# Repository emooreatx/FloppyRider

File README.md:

# FloppyRider

Full-featured DIY PC-compatible 8-inch Diskette drive based on the IBM 51TD.

## Project events

__New enclosure and AC power supply (v1.0) (2023/05/02)__

__Third revision of the controller (v2.1) (2022/12/03): Added an improved write protection mechanism and support for installing an external write protection switch.__ __Fabrication files released: [V2 fabrication files](./pcb)__

__Second revision (2022/06/24):__ I have added a transistor to drive the write/erase-gate signals on the IBM drive. I have noticed that write/erase-gate have a very low input impedance (90 ohms each, could that be a safety measure to make harder to accidentally drive the signal high?) that is way over-spec for the 74LS logic to drive properly. The prototype worked by pure luck but trying with other 74LS components the signal level was too low to enable the gates so the device was only capable of reading. The solution is to include a transistor to drive that signals up to acceptable levels.

__Initial release (2022/06/09)__

## Introduction

This project shows how to create an adapter to be able to use IBM 8-inch Diskette drives with a standard PC floppy controller. It includes a controller/adapter, power supply and 3D-printed enclosure designed to connect an IBM 51TD disk drive to a regular PC floppy controller.

In theory it may work also with IBM 31SD drives but I don't have one so it is untested for them.

The current production version is capable of reading, writing and formatting Diskette 1,Diskette 2 (SD) and Diskette 2D (DD) types on a 51TD disk drive.

The IBM 51TD was used in the IBM Displaywriter, System/36, System/38, and other machines.

If you like it or want to make your unit drop me a message to inmbolmie [AT] gmail.com

## Videos

Video showing general operation connected to an IBM 5160: [FloppyRider 8-inch drive for PCs](https://www.youtube.com/watch?v=_m2nTry7Z7E)

Video showing the adapter in action, here it is used to make an 8-inch diskette MSDOS-bootable: [Booting MSDOS from an IBM 51TD 8-inch drive](https://www.youtube.com/watch?v=TbLUqG_d6FU)

Using the adapter to image a 33FD-formatted diskette with Imagedisk: [Imaging on a PC an IBM 8-inch diskette with a 51TD diskette drive, Imagedisk and FloppyRider](https://www.youtube.com/watch?v=4pZ3qMAHVGs)

This project was inspired by CuriousMarc's video about data recovery from 8-inch floppies. This kind of converter is something Master Ken would have made like in five minutes using a Teensy, in case they wanted to use a genuine IBM Diskette drive in their data recovery adventure.

[Fossil Data Part 2: 8-Inch IBM Floppy Data Recovery](https://www.youtube.com/watch?v=5FVwheTVWko)

## Hardware

There are three main components on this project, the drive controller, the power supply and the 3D-printed enclosure

### Drive controller

The adapter hardware is pretty straightforward and can be made cheapily with very low-cost components:

* Pin headers and IDC ribbon cables
* JST-XH 5A Connector for DC input
* Arduino ProMicro microcontroller board (5V)
* 74LS02
* 74LS06
* 74LS08
* 74LS74
* 12x1K resistors
* 1x4,7K resistor
* NPN transistor

### Power supply

The 31SD and 51TD disk drives have pretty hefty power requirements, as you will need to provide them with:

* AC mains power for the disk rotating motor (on a separate connector)
* +24V at 12W (on the 36-pin idc connector)
* +5V (on the 36-pin idc connector)
* -5V (on the 36-pin idc connector)

I have designed a custom power supply based on discrete AC-DC and DC-DC converters. It is not so cheap to make as the controller as the discrete converters are expensive. The required components are:

* MeanWell IMR-20-24 AC to +24V DC conversion module
* Traco Power TEN 6-2421N DC to +-5V DC conversion module
* JST-XH 5A Connector for DC output
* 3x100uF 50V aluminium electrolytic capacitors
* Schurter DD21.0124.1111 AC plug module
* Schurter 4301.1024.26 fuse holder
* TE Connectivity / AMP 350834-4 connector
* 1A AC fuses

The power supply is fused, cuts both phases on AC input when switched off and connects protective earth to protective earth on the drive connector. The individual modules provide also short-circuit and overload protection.

__Warning, the power supply is compatible with both 110V and 220V drives through the IMR-20-24 module, but does not make any conversion on the AC input that is passed directly to the drive motor. So even with this supply you cannot use a 110V drive on 220V AC line or a 220V drive on 110V AC line. So make sure that your drive is compatible with your AC line voltage__

### 3D-printed enclosure

Having a naked 51TD isn't ideal for extended use so I have designed a 3D-printed case that can be made using regular printers and is inspired on the IBM drive enclosures of the era.

Note that this is a BIG print job, has many parts and can take like a full week of non-stop printing to make. It is also tricky to assemble, as some parts have to be glued-in to keep the part design and printing as simple as possible. The total printing material required is around 850-1000 grams depending on the infill used on some parts.

You also need at least a 270 x 210mm sized 3d-printer bed to be able to print this. The biggest pieces measured by printed area are the side panels.

I include STL files for all the parts as well as the Freecad 3D model.

You can get the STL and design files in the __case__ directory.

## Software

You can get the Arduino source code for the ProMicro in the __FloppyRider__ directory. You can program it using the regular Arduino IDE.

## KiCad Project

You can get the current project files in the __KiCad__ directory. The PCB design files and gerbers are now available if you want to make your own boards :  [V2 fabrication files](./pcb)

Note that the files have been created with Kicad v6.

## Warning about some floppy controllers

It seems that some floppy controllers may ground the signals to the floppy drive when the computer is switched off. If you have a diskettte inserted and engaged when this happens, that can lead to the track where the head is currently positioned to be erased.

If you are working with important media be careful about this, and __turn on the disk drive only after the computer is switched on, and remove the diskette or the power to the disk drive before the computer is switched off.__

__The version 2 board improves this situation__ because when the write protection switch is engaged, the Write/Erase Gate signals for the 8" drive are physically disconnected from the incoming write signals, so you won't accidentally erase any data __if write protection is engaged__, even if the host floppy controller grounds all the interface signals. This makes the adapter safer for using in disk imaging tasks.

## Operation

These are the main points that need to be carried out for conversion:

#### Logic levels

The PC floppy signals are open collector low-level active, while the IBM signals are push-pull high-active. The 74 series chips provide most of the conversion.

All the signals are gated by the "drive select" PC signal for the adapter to be able to operate with another floppy drive on the same cable.

#### Track addressing

The PC floppy adresses tracks by a "direction" and "step" signal, and gets a "track 0" signal when the head is placed at such track. The IBM interface lacks a "track 0" signal and you control direcly the stepper motor signals "access 0" and "access 1". The ProMicro initializes the head position at track 0 at startup. From there it gets track of where the head is actually positioned and translates the required signals on both sides.

#### Write data signal.

The PC floppy write data signal generates a full pulse (falling and rising edge) for each magnetic flux transition that needs to be recorded on the disk surface, while in the IBM interface the "write data" signal records a magnetic flux transition for each signal level change (rising or falling edge). The conversion is made via the 74LS74 flip-flop.

## Connection

__As the connectors carry a powerful +24V signal, connector orientation is critical and getting it wrong, reversing or misplacing it could damage your hardware.__

### Option A: Power the drive from a compatible host system

The easier way to get all the required power rails is getting them from the original host hardware where the disk drive is enclosed. For that reason a 36-pin host connector header is provided. Note that the connector sides are mirrored to be able to use it with a cable-to-cable connection. The adapter will be placed as a bridge between the host cable and the disk drive header.

The other 36-pin header will be used with a regular IDC ribbon cable connector to connect it to the disk drive. Note that you won't be _easily_ able to use the most common 40-pin cables as the available space for the connector in the disk drive is very limited.

Not that "Pin B1" position is indicated on the silkscreen of the PCB.

### Option B: Power the drive from the independent power supply

If you have the FloppyDriver independent power supply capable of providing the required DC levels you can leave the 36-pin host pin header unconnected and provide power via a separate 5-pin JST-XH connector.

### Connection to the PC drive controller

On the other end of the adapter you have a 34-pin header for the PC standard floppy cable. The adapter is hard-wired for drive B as most PC floppy drives are.

Not that "Pin 1" position is indicated on the silkscreen of the PCB.

## External write protection

A 6-pin 2x3 pin header is provided to be able to connect an external SPDT write protection switch. In case of __using the external write protection switch, the on-board switch has to be placed in the ON position and jumper JP1 has to be removed__. Then you can control the ON-OFF write protection status from the external switch.

On the contrary, __if you are using the on-board write protection switch, the JP1 jumper has to be installed__. The jumper is not safety-critical though, as the effect of not installing it will be that the host controller will consider the write protection always disabled, but the drive will be write-protected anyway if the write protection switch is in the ON position.

## Schematics

As currently working on the production units. Subject to further modification

## PCB

Sample image of the PCBs from Kicad.

## 3D-printed case fabrication and assembly

This enclosure has been designed to be reasonably easy to print on a 3D printer with a 270 x 210mm sized bed, on regular PLA filament and in a maximum of 14 hours of printing for a single piece.

With 2mm thick walls the case is sturdy enough to be convenient to carry around the assembled unit, but obviously doesn't have the rigidity of a full-metal or ABS injection-molded enclosure.

It is designed to be assembled using 10mm M4 DIN-965 bolts and nuts. A couple of M3 bolts and nuts are also required for the power supply, and four 5mm M2,5 bolts for the controller PCB attachment. The nuts have to be soldered to the enclosure with the superglue-soda method on some places and some pieces have to be glued together. That minimal assembly allows to simplify the piece design and all the pieces can be printed without supports. In reality it would be better to print 3mm thick walls to get a better mount for the M4 bolts (they will protrude a little on 2mm walls) but that would increase notably the printing times.

Of course you can also reduce the times increasing the layer height. I printed eveything at 0,2mm layer height but 0,3 or 0,4mm could be more convenient.

All the pieces have been printed on regular PLA, no supports, 0,2mm layer heigh, infill 100% except for the base that was printed with 20% infill. The printing time for the big pieces on my printer is between 7 and 14 hours (14 for back panel). In total it took me around a week to print everything, one big piece each day. In total I used approx. 850 grams of 1,75mm filament.

Now I will give some assembly tips.

There are two versions of the front panel, one with a window for a 25x25mm badge and one without it.

To assemble the unit first you have to join the front panel to the base with two bolts and two nuts. You will have to drill the holes on the front panel baseas they are not included. These like other holes are not included because I think that drilling them yourself will give a better piece alignment. Drill them with a 4mm drill.

For the back panel the attachment is similar but you will have to be able to remove it without access to the nuts so the nuts will have to be fixed with the superglue+soda method or any other similar system. That way you will be able to tighten the bolts from under the base when the drive is in place

Now place the drive inside and align it to the holes on the right side (looking from the front) panel and the right side of the front panel. Be gentle with the front lever of the unit as it is quite fragile, it has to be engaged to go inside the slit.

The left panel will be far from the drive, so you will have to print three drive fitting blocks and solder them to the base using superglue like shown here (there is another place not shown on the picture to place a fitting to the right). The inner fitting is for the drive and the outer fitting is for the panel. You can in theory use very long M4 bolt to stick the panel to the drive, but it is better to use two 10mm short bolts instead. The holes on the fittings have to be aligned to the holes on the drive and panel.

You have to assemble also four panel fittings on top of the front and back pieces to secure the side panels. They are shown on the first picture near the top. They have a nut each on back. Be sure to align them to the holes on the side panels. On the final design the fittings are a little lower than on the picture because I discovered that they interferred with the power supply pcb position and because of that they were tricky to fix to the back panel.

To align the fittings it would be more convenient to separate the front and back panels from the base. Now prepare the top, left and right panels that have to be glued together. Then put everything upside down together and attach and glue the fittings to the front and back panels.

Now prepare the cable, you need approx. a 60cm 36-pin IDC ribbon cable. Note that the drive pin header is a tight fit for the cable, so you cannot use anything else bigger, like the more common 40-pin ribbon cable connectors.

The cable goes under the drive. There is a channel made on the base to allow the cable to go under the drive mounting feet.

Check carefully for Pin-1 position. On the picture the red cable indicates pin-1 and goes to the left of the connector as seen looking the drive from the right side.

Now prepare the back panel, mounting the power supply with M3 bolts and nuts. The controller is mounted on top of the PCB-holder piece using M2,5 bolts. Connect the supply and the controller using a suitable 5-pin JST-XH cable. Connect the drive 36-pin ribbon cable before the controller is assembled. Check carefully for pin-1 position, on the PCB is marked as "Pin B1". Note that the red cable goes to that side.

Do not forget to put in place the write protection switch between the controller and the back panel. You will need to drill a 2mm hole in the center of the switch to slide it onto the switch lever mounted on the PCB. To insert it you have to bend the back "ears" and straighten them again after inserted. The on-board swith is very simple, you may want to change it for a proper external SPDT switch as the controller PCB supports it.  

Switch to the right is write protected, switch to the left is write enabled. I didn't include any lettering to keep the printing simple, but you can add it or put on a sticker to indicate it.

Now you can put in place the back panel and tighten the bolts from under the base to hold it in position.

When the panel is in, place attach the 51TD power connector to the power supply. This connector can only go one way.

Now finally mount the center section. The top, left and right panels were already glued together. Attach them using M4 bolts to the drive on the left, to the fitting glued to the base on the right, and to the front and back panels on the top using four bolts. Do not overtighten anything as you risk to rip the nuts from the pieces and in general is not needed.

This a sample of how could the unit look on the back connected to a PC. If you are going to have a setup like this add some anti-slip rubber feet under the drive base.

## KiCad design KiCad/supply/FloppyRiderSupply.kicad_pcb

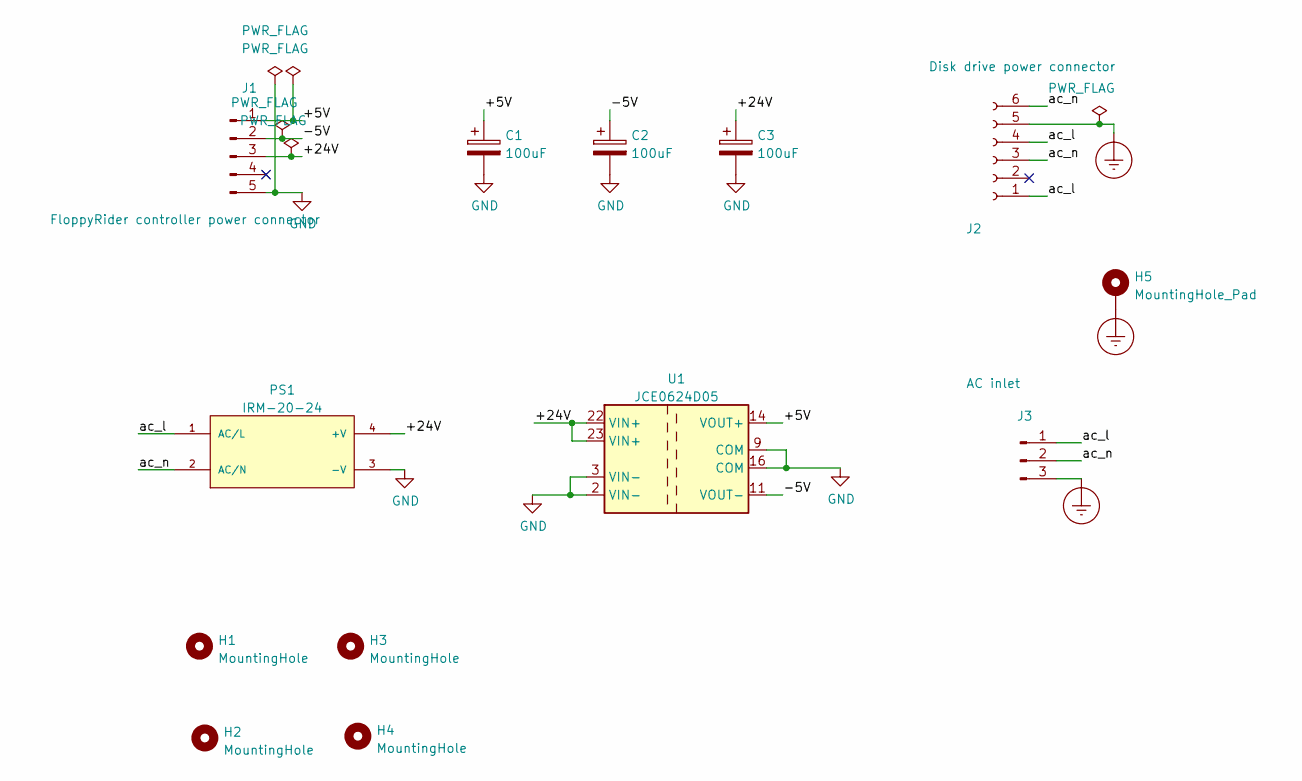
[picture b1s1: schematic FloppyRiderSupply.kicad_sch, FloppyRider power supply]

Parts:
C1, C2, C3: 100uF; CP_Radial_D10.0mm_P3.50mm
H1, H2, H3, H4: MountingHole; MountingHole_3.2mm_M3
H5: MountingHole_Pad; MountingHole_3.2mm_M3_Pad
J1: FloppyRider controller power connector; PinHeader_1x05_P2.54mm_Vertical
J2: Disk drive power connector; 350834-4
J3: AC inlet; DD21.0124.1111
PS1: IRM-20-24; CONV_IRM-20-24
U1: JCE0624D05; Converter_DCDC_XP_POWER_JTExxxxDxx_THT

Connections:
/+5V: C1.1, J1.1, U1.14 (VOUT+)
/+24V: C3.1, J1.3, PS1.4 (+V), U1.22 (VIN+), U1.23 (VIN+)
/-5V: C2.1, J1.2, U1.11 (VOUT-)
/ac_l: J2.1, J2.4, J3.1, PS1.1 (AC/L)
/ac_n: J2.3, J2.6, J3.2, PS1.2 (AC/N)
Earth_Protective: H5.1, J2.5, J3.3
GND: C1.2, C2.2, C3.2, J1.5, PS1.3 (-V), U1.2 (VIN-), U1.3 (VIN-), U1.9 (COM), U1.16 (COM)

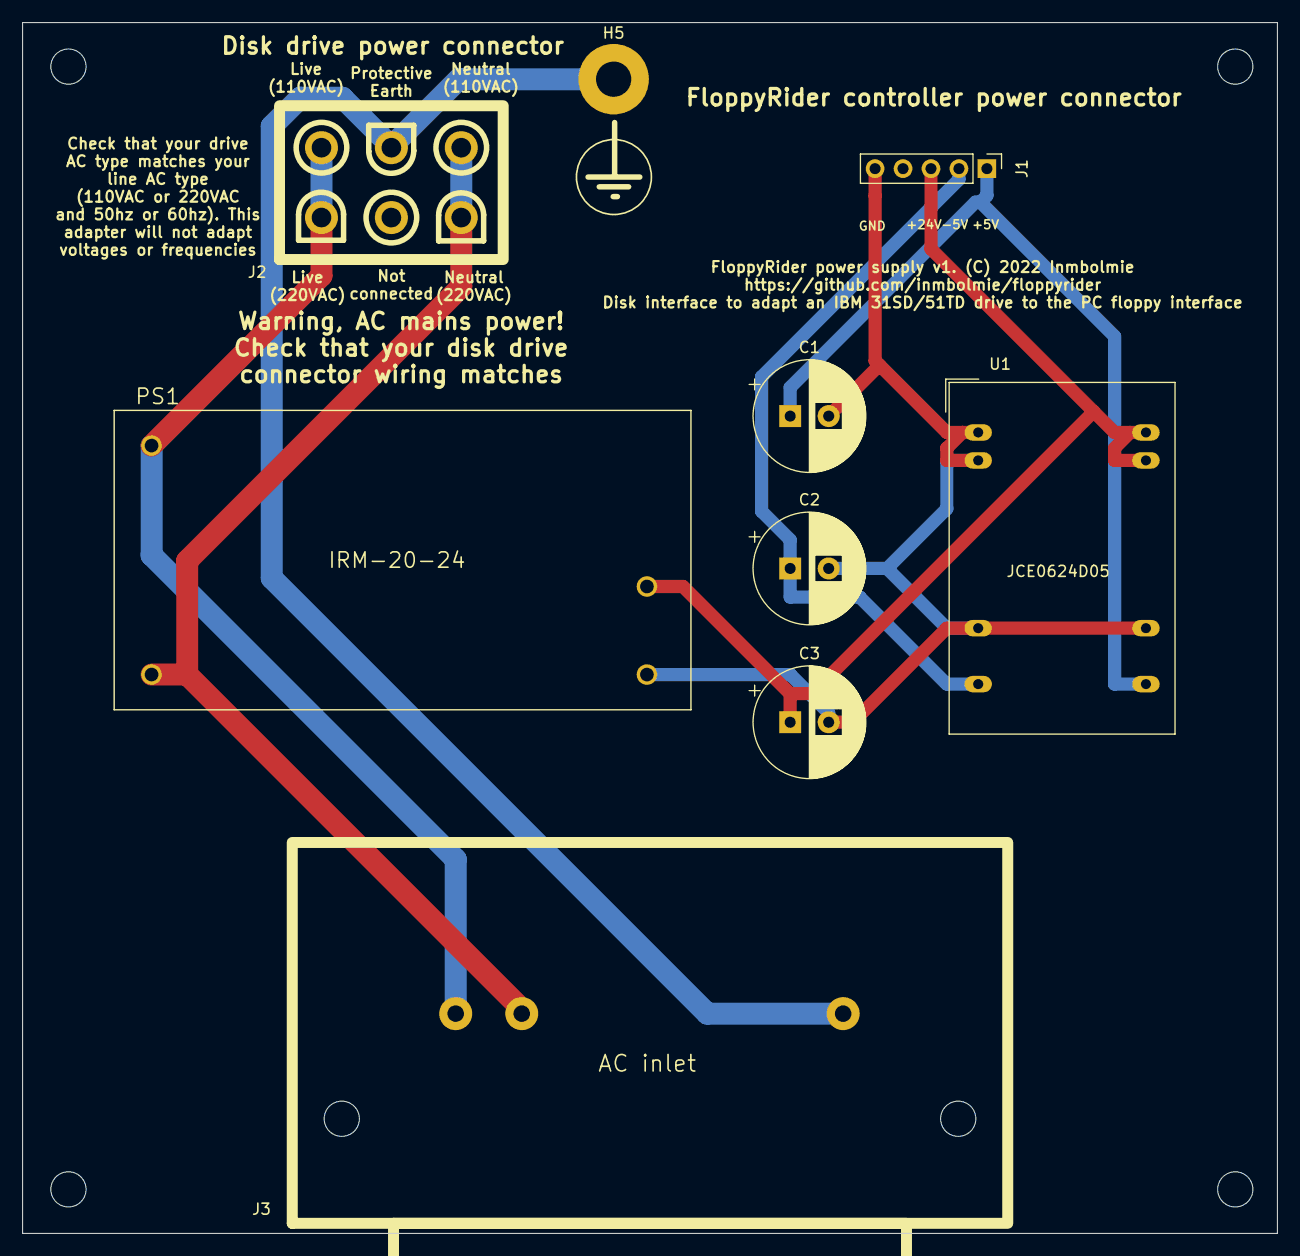
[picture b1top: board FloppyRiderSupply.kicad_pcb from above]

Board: 2 copper layers, 114.0 x 110.0 mm, 13 parts (0 on the bottom side), 7 nets.

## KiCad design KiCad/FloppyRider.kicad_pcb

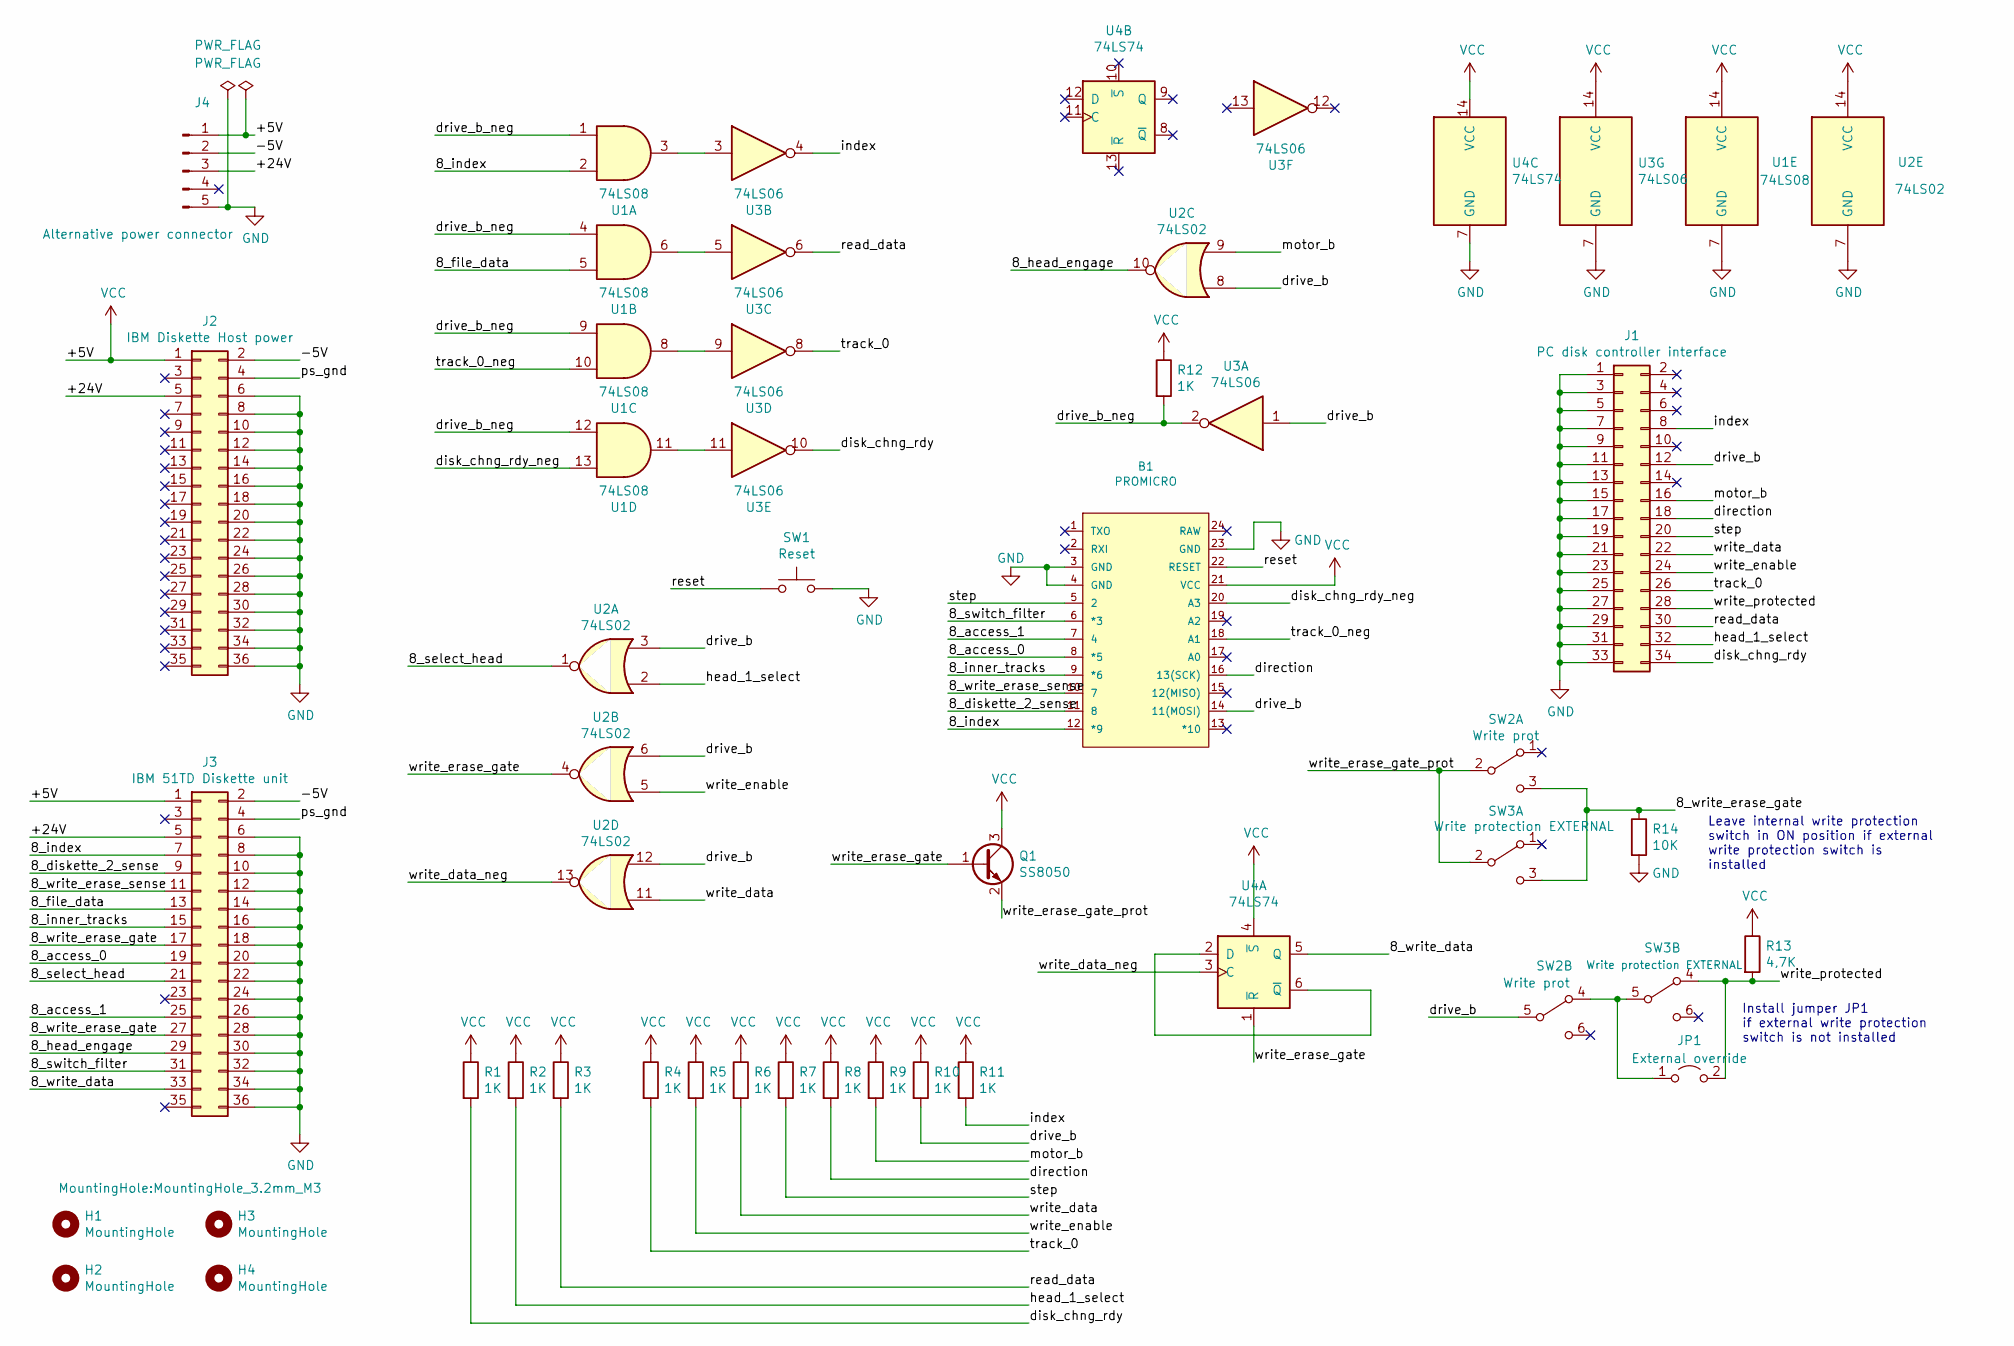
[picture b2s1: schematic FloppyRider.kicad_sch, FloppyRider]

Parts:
B1: PROMICRO; SPARKFUN_PRO_MICRO
H1, H2, H3, H4: MountingHole; MountingHole_3.2mm_M3
J1: PC disk controller interface; PinHeader_2x17_P2.54mm_Vertical
J2: IBM Diskette Host power; PinHeader_2x18_P2.54mm_Vertical
J3: IBM 51TD Diskette unit; PinHeader_2x18_P2.54mm_Vertical
J4: Alternative power connector; PinHeader_1x05_P2.54mm_Vertical
JP1: External override; PinHeader_1x02_P2.54mm_Vertical
Q1: SS8050; SOT-23; LCSC C2150
R1, R2, R3, R4, R5, R6, R7, R8, R9, R10, R11, R12: 1K; R_0603_1608Metric; LCSC C21190
R13: 4,7K; R_0603_1608Metric; LCSC C23162
R14: 10K; R_0603_1608Metric; LCSC C25804
SW1: Reset; SW_Push_1P1T_NO_6x6mm_H9.5mm; LCSC C221880
SW2: Write prot; SW-TH_K3-2235S-K1; LCSC C223859
SW3: Write protection EXTERNAL; PinHeader_2x03_P2.54mm_Vertical CUSTOM
U1: 74LS08; SO-14_3.9x8.65mm_P1.27mm
U2: 74LS02; SO-14_3.9x8.65mm_P1.27mm
U3: 74LS06; SO-14_3.9x8.65mm_P1.27mm; LCSC C113682
U4: 74LS74; SO-14_3.9x8.65mm_P1.27mm; LCSC C39990

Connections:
/8_access_0: B1.8 (*5), J3.19
/8_access_1: B1.7 (4), J3.25
/8_diskette_2_sense: B1.11 (8), J3.9
/8_file_data: J3.13, U1.5
/8_head_engage: J3.29, U2.10
/8_index: B1.12 (*9), J3.7, U1.2
/8_inner_tracks: B1.9 (*6), J3.15
/8_select_head: J3.21, U2.1
/8_switch_filter: B1.6 (*3), J3.31
/8_write_data: J3.33, U4.5 (Q)
/8_write_erase_gate: J3.17, J3.27, R14.1, SW2.3 (C), SW3.3 (C)
/8_write_erase_sense: B1.10 (7), J3.11
/+24V: J2.5, J3.5, J4.3
/-5V: J2.2, J3.2, J4.2
/direction: B1.16 (13(SCK)), J1.18, R8.2
/disk_chng_rdy: J1.34, R1.2, U3.10
/disk_chng_rdy_neg: B1.20 (A3), U1.13
/drive_b: B1.14 (11(MOSI)), J1.12, R10.2, SW2.5 (B), U2.3, U2.6, U2.8, U2.12, U3.1
/drive_b_neg: R12.2, U1.1, U1.4, U1.9, U1.12, U3.2
/head_1_select: J1.32, R2.2, U2.2
/index: J1.8, R11.2, U3.4
/motor_b: J1.16, R9.2, U2.9
/ps_gnd: J2.4, J3.4
/read_data: J1.30, R3.2, U3.6
/reset: B1.22 (RESET), SW1.1
/step: B1.5 (2), J1.20, R7.2
/track_0: J1.26, R4.2, U3.8
/track_0_neg: B1.18 (A1), U1.10
/write_data: J1.22, R6.2, U2.11
/write_data_neg: U2.13, U4.3 (C)
/write_enable: J1.24, R5.2, U2.5
/write_erase_gate: Q1.1 (B), U2.4, U4.1 (~R)
/write_erase_gate_prot: Q1.2 (E), SW2.2 (B), SW3.2 (B)
/write_protected: J1.28, JP1.2 (B), R13.2, SW3.4 (A)
GND: B1.3 (GND), B1.4 (GND), B1.23 (GND), J1.1, J1.3, J1.5, J1.7, J1.9, J1.11, J1.13, J1.15, J1.17, J1.19, J1.21, J1.23, J1.25, J1.27, J1.29, J1.31, J1.33, J2.6, J2.8, J2.10, J2.12, J2.14, J2.16, J2.18, J2.20, J2.22, J2.24, J2.26, J2.28, J2.30, J2.32, J2.34, J2.36, J3.6, J3.8, J3.10, J3.12, J3.14, J3.16, J3.18, J3.20, J3.22, J3.24, J3.26, J3.28, J3.30, J3.32, J3.34, J3.36, J4.5, R14.2, SW1.2, U1.7 (GND), U2.7 (GND), U3.7 (GND), U4.7 (GND)
unnamed: JP1.1 (A), SW2.4 (A), SW3.5 (B)
unnamed: U1.3, U3.3
unnamed: U1.6, U3.5
unnamed: U1.8, U3.9
unnamed: U1.11, U3.11
unnamed: U4.2 (D), U4.6 (~Q)
VCC: B1.21 (VCC), J2.1, J3.1, J4.1, Q1.3 (C), R1.1, R2.1, R3.1, R4.1, R5.1, R6.1, R7.1, R8.1, R9.1, R10.1, R11.1, R12.1, R13.1, U1.14 (VCC), U2.14 (VCC), U3.14 (VCC), U4.4 (~S), U4.14 (VCC)

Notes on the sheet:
Install jumper JP1 if external write protection switch is not installed
Leave internal write protection switch in ON position if external write protection switch is installed

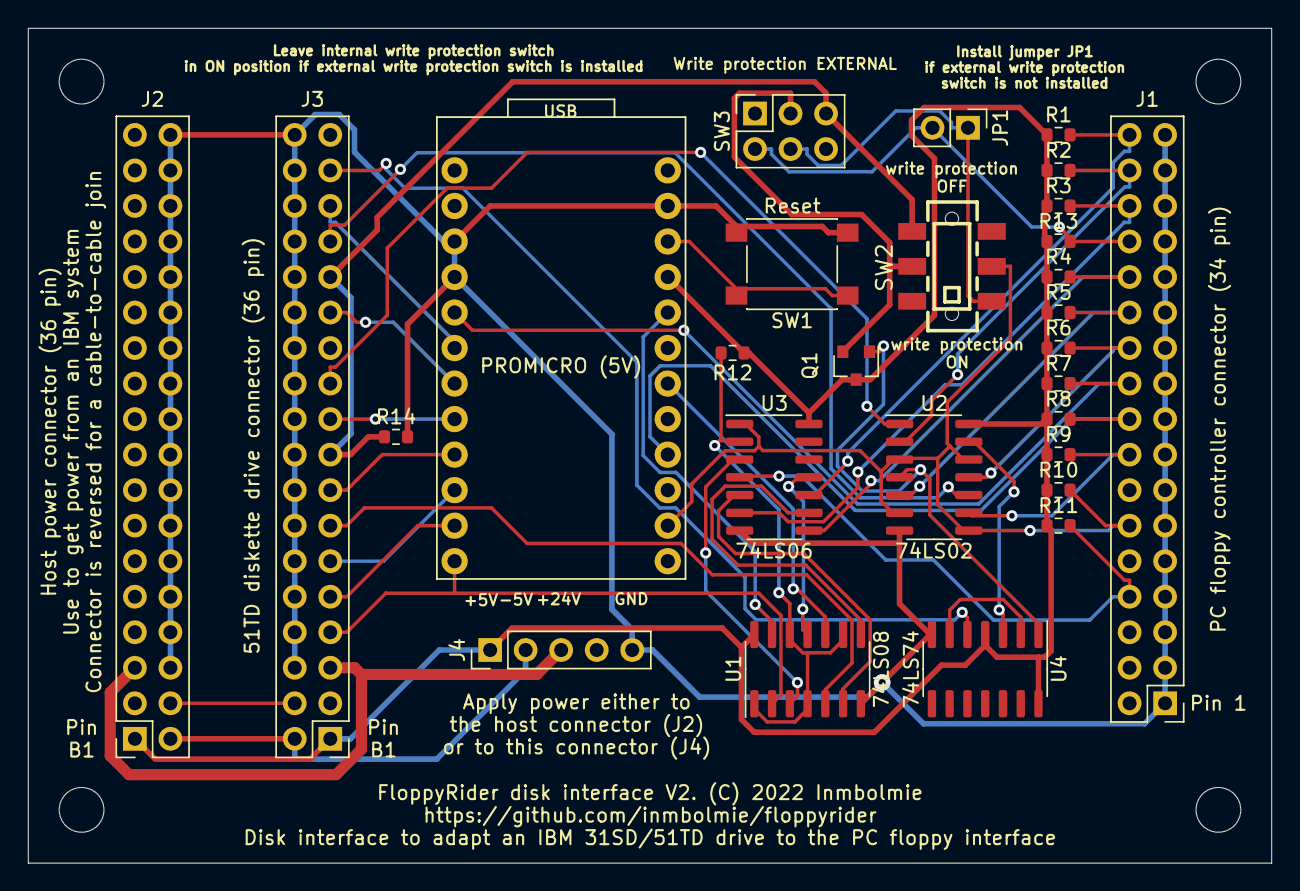
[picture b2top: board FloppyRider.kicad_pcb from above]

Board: 2 copper layers, 88.9 x 59.7 mm, 32 parts (0 on the bottom side), 42 nets.

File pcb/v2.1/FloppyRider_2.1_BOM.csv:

Comment,Designator,Footprint,LCSC
SS8050,Q1,Package_TO_SOT_SMD:SOT-23,C2150
1K,"R1,R2,R3,R4,R5,R6,R7,R8,R9,R10,R11,R12",Resistor_SMD:R_0603_1608Metric,C21190
"4,7K",R13,Resistor_SMD:R_0603_1608Metric,C23162
10K,R14,Resistor_SMD:R_0603_1608Metric,C25804
Write prot,SW2,dpdt_2:SW-TH_K3-2235S-K1,C223859

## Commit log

2022-12-03 Version 2 board
2023-05-05 New standalone power supply and 3D-printed enclosure
2023-12-24 Add details on how the IBM 51TD was used

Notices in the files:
KiCad/FloppyRider.kicad_pcb:
FloppyRider disk interface V2. (C) 2022 Inmbolmie
KiCad/supply/FloppyRiderSupply.kicad_pcb:
FloppyRider power supply v1. (C) 2022 Inmbolmie
